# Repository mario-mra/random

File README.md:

# random
Random stuff, that's It!

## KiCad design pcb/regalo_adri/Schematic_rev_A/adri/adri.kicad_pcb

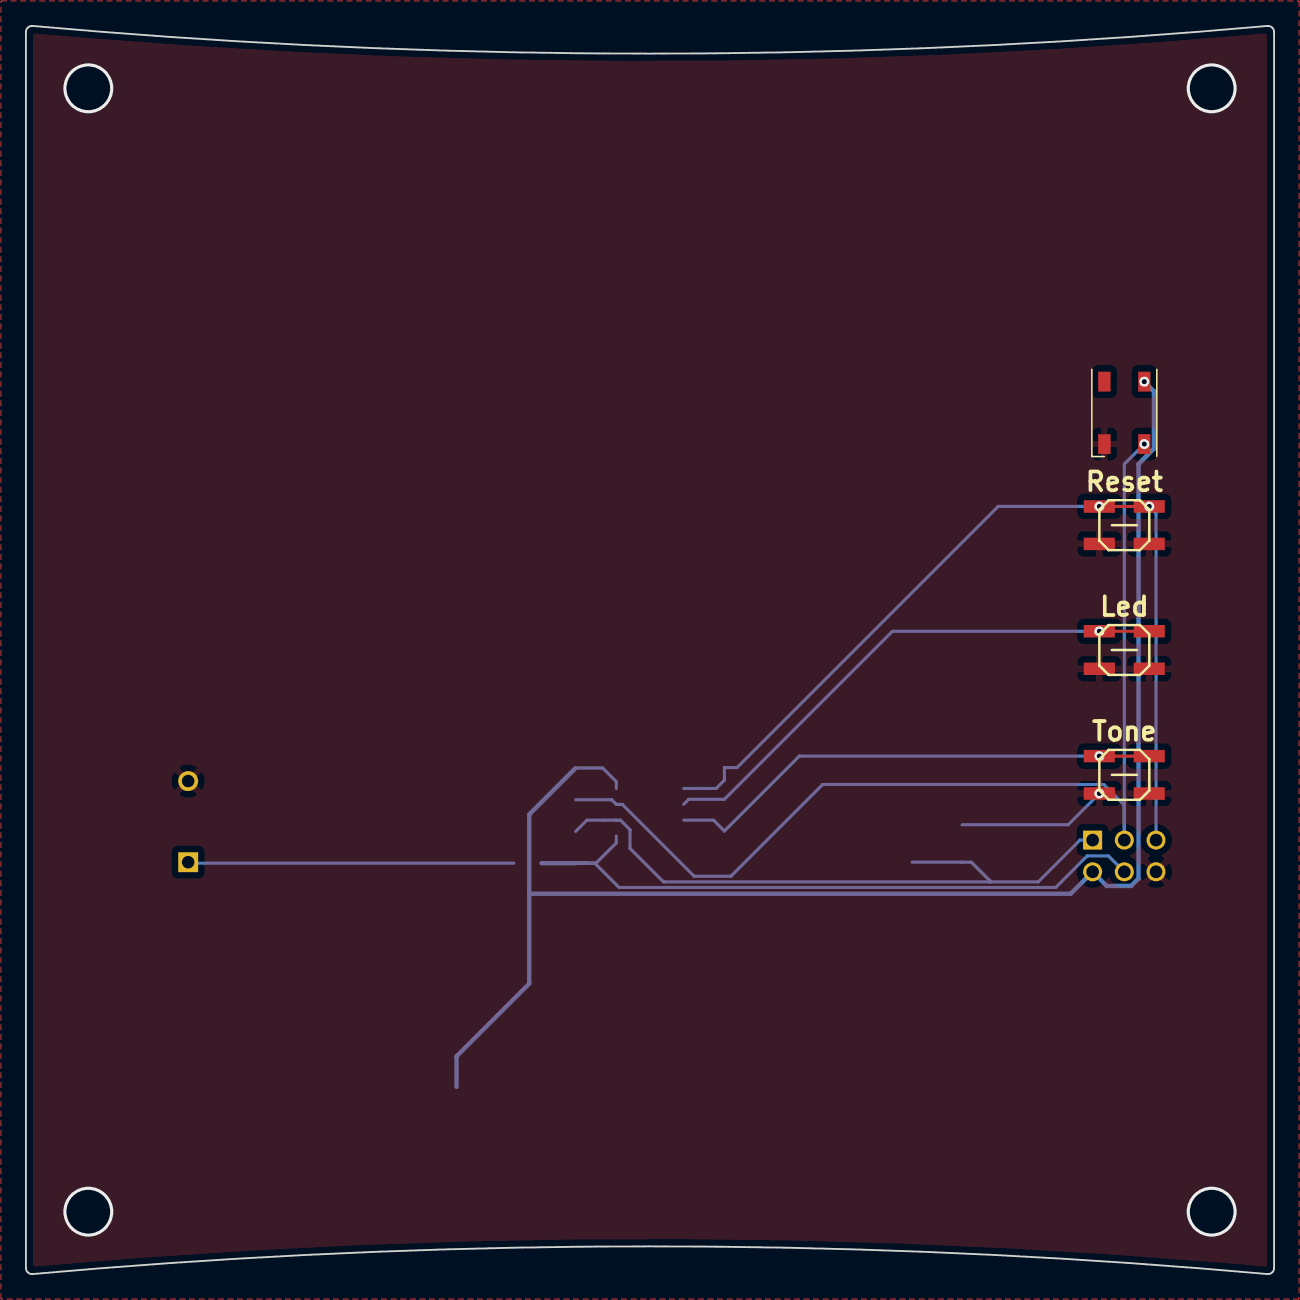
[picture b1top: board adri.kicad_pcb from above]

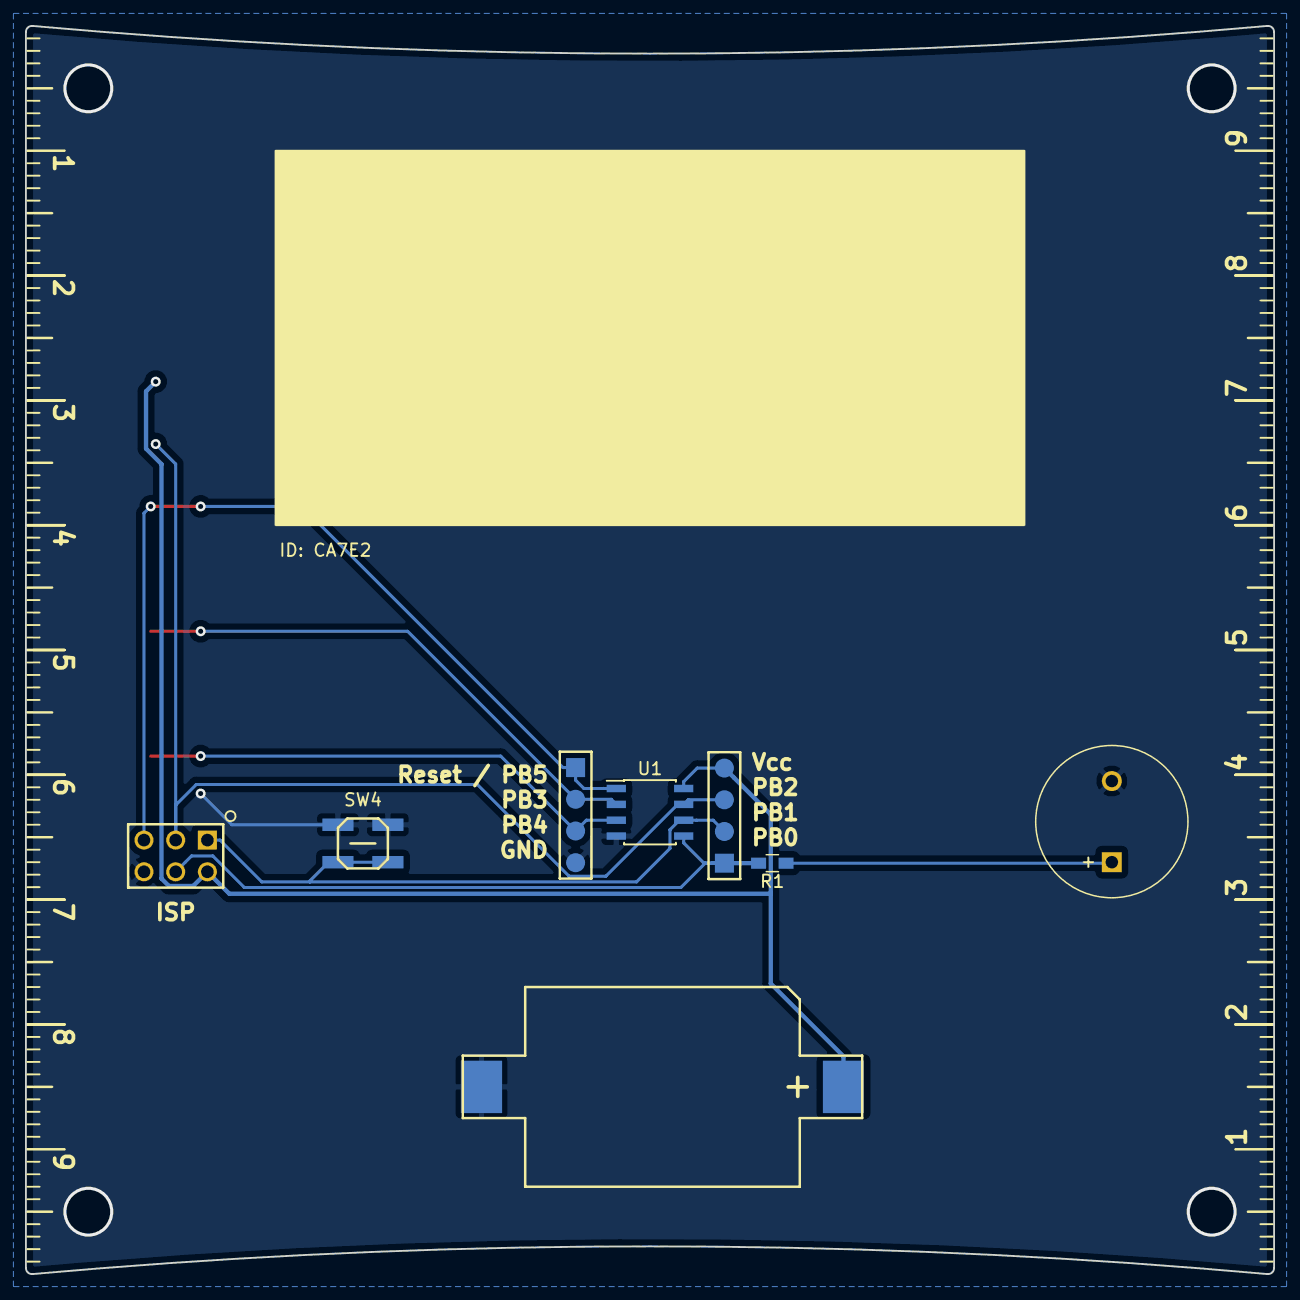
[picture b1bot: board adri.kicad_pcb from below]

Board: 2 copper layers, 100.0 x 100.0 mm, 12 parts (8 on the bottom side), 9 nets.

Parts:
BZ1: Buzzer; MagneticBuzzer_ProSignal_ABT-410-RC
Batt1: Batt_cr2032; Batt_cr2032_SMD
D1: WS2812B; LED_WS2812B-PLCC4
J1: AVR-ISP-6; AVR-ISP-6-TH
J2, J3: Conn_01x04_Female; 4_pin_conn_SMD
R1: R; R_0603_HandSoldering
SW1, SW2, SW3, SW4: SW_Push; SW_ali_4x4x0.8
U1: ATtiny13V-10SSU; SOIC-8_3.9x4.9mm_Pitch1.27mm

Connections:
+BATT: Batt1.1, D1.1, J1.2, J3.4, U1.8
GND: BZ1.2, Batt1.2, D1.3, J1.6, J2.4, SW1.1, SW2.1, SW3.1, SW4.1, U1.4
unnamed: BZ1.1, R1.1
unnamed: D1.4, J1.3, J3.3, U1.7
unnamed: J1.1, J3.2, SW4.2, U1.6
unnamed: J1.4, J3.1, R1.2, U1.5
unnamed: J1.5, J2.1, SW1.2, U1.1
unnamed: J2.2, SW3.2, U1.2
unnamed: J2.3, SW2.2, U1.3

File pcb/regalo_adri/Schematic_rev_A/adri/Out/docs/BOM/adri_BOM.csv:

"Id";"Designator";"Package";"Quantity";"Designation";"Supplier and ref";
1;"REF**,REF**,REF**,REF**,REF**,REF**,REF**,REF**,REF**,REF**,REF**,REF**,REF**,REF**,REF**,REF**";"ruler_1cm";16;"ruler_1cm";;;
2;"REF**,REF**,REF**,REF**";"ruler_1cm_B";4;"ruler_1cm_B";;;
3;"Batt1";"Batt_cr2032_SMD";1;"Batt_cr2032";;;
4;"BZ1";"MagneticBuzzer_ProSignal_ABT-410-RC";1;"Buzzer";;;
5;"D1";"LED_WS2812B-PLCC4";1;"WS2812B";;;
6;"J1";"AVR-ISP-6-TH";1;"AVR-ISP-6";;;
7;"R1";"R_0603_HandSoldering";1;"R";;;
8;"SW1,SW2,SW3,SW4";"SW_ali_4x4x0.8";4;"SW_Push";;;
9;"U1";"SOIC-8_3.9x4.9mm_Pitch1.27mm";1;"ATtiny13V-10SSU";;;
10;"J2,J3";"4_pin_conn_SMD";2;"Conn_01x04_Female";;;
11;"G***";"ITI";1;"LOGO";;;

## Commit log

2018-09-21 PCB Gift & custom bash command
2018-09-25 Text to SVG file
2018-09-25 Removed unused parameter
2018-11-27 Add Firefox .desktop file in light mode
2018-11-27 ringzer0ctf_challenges
